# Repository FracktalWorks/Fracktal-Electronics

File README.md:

# Fracktal-Electronics
Repository for the Miscellaneous Hardware components and boards used for the additional features and other external devices

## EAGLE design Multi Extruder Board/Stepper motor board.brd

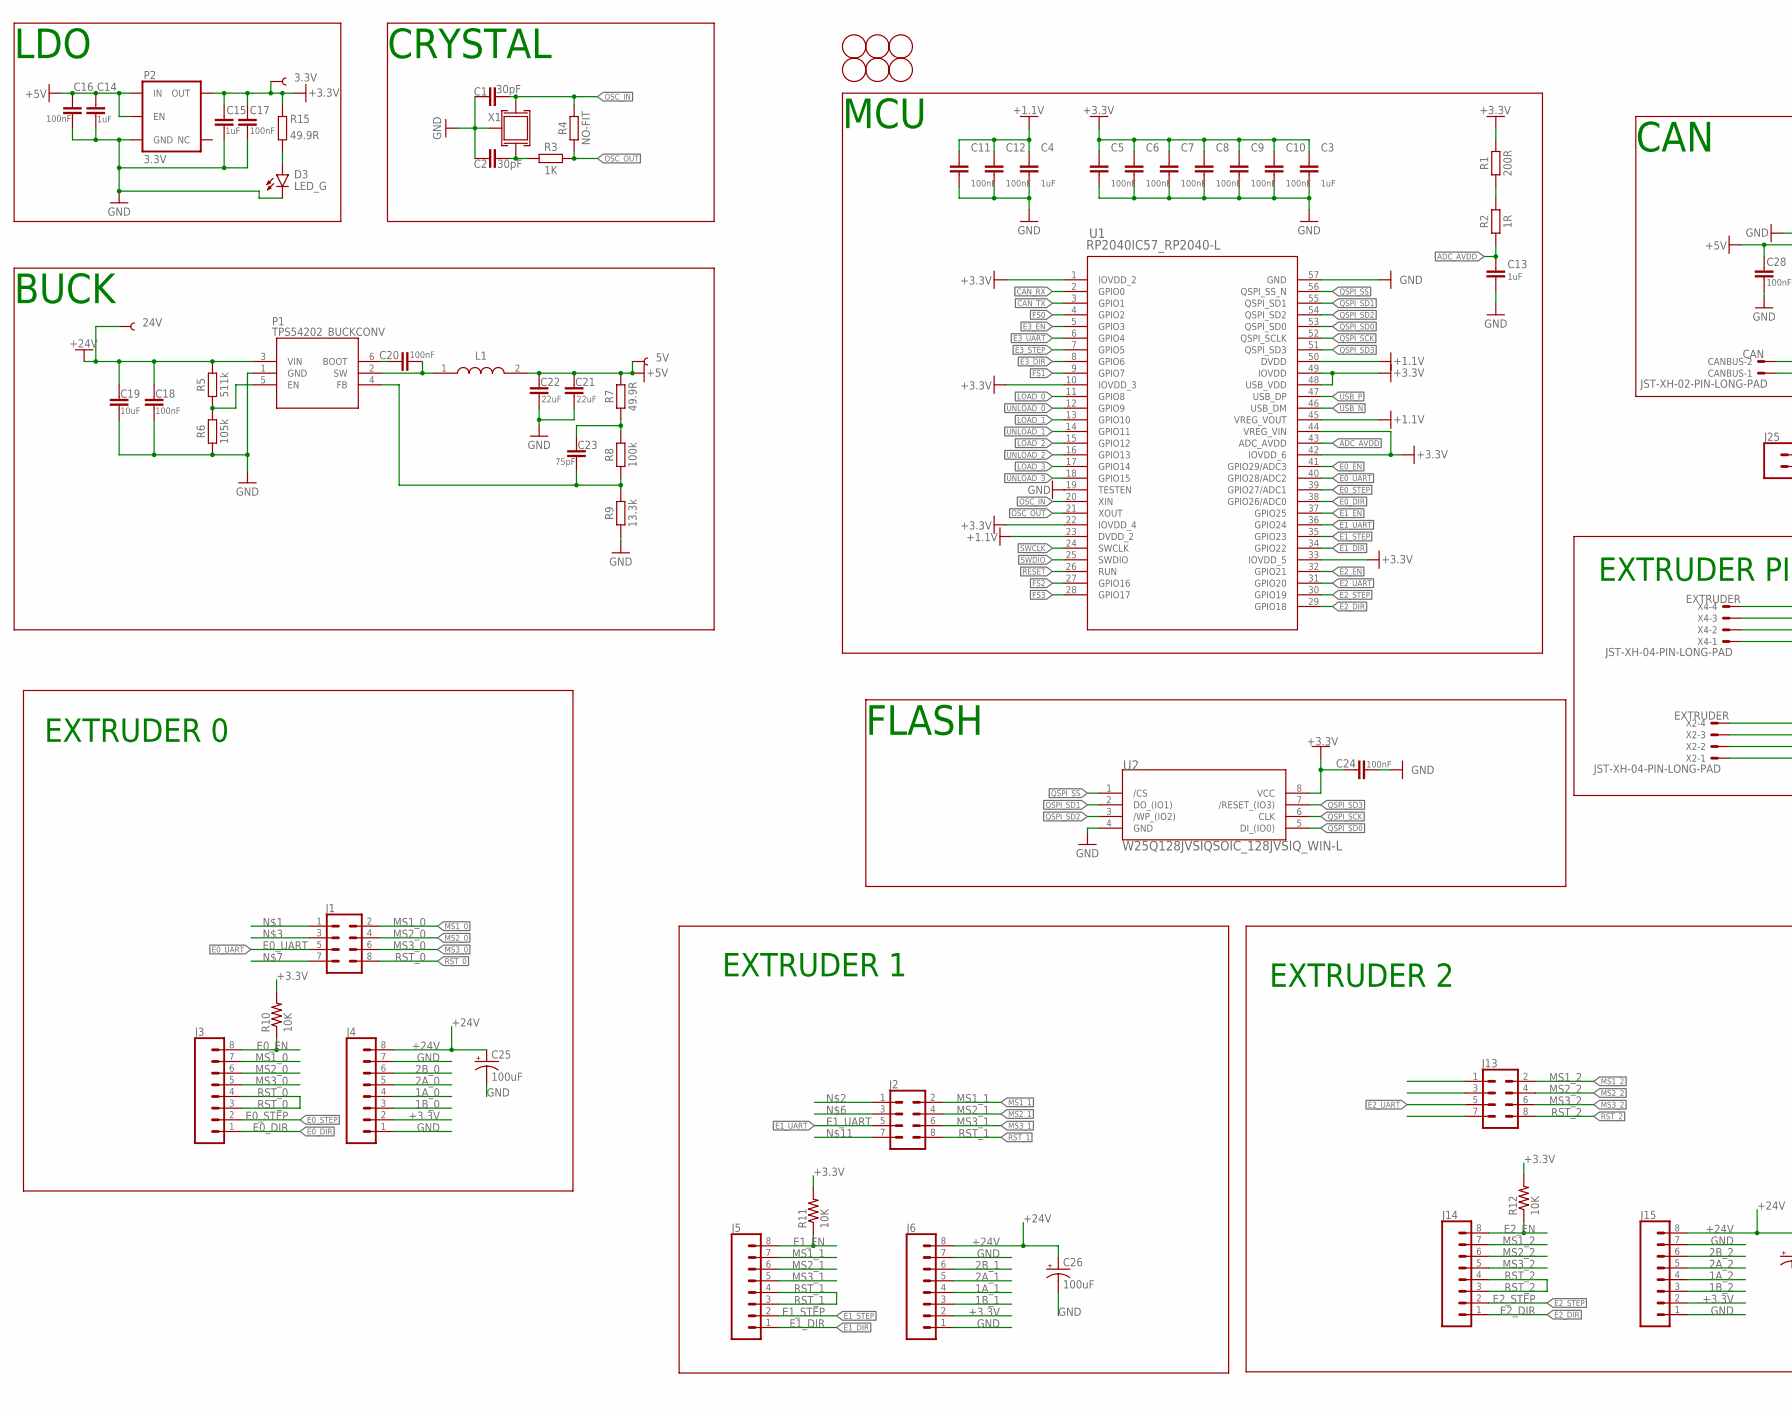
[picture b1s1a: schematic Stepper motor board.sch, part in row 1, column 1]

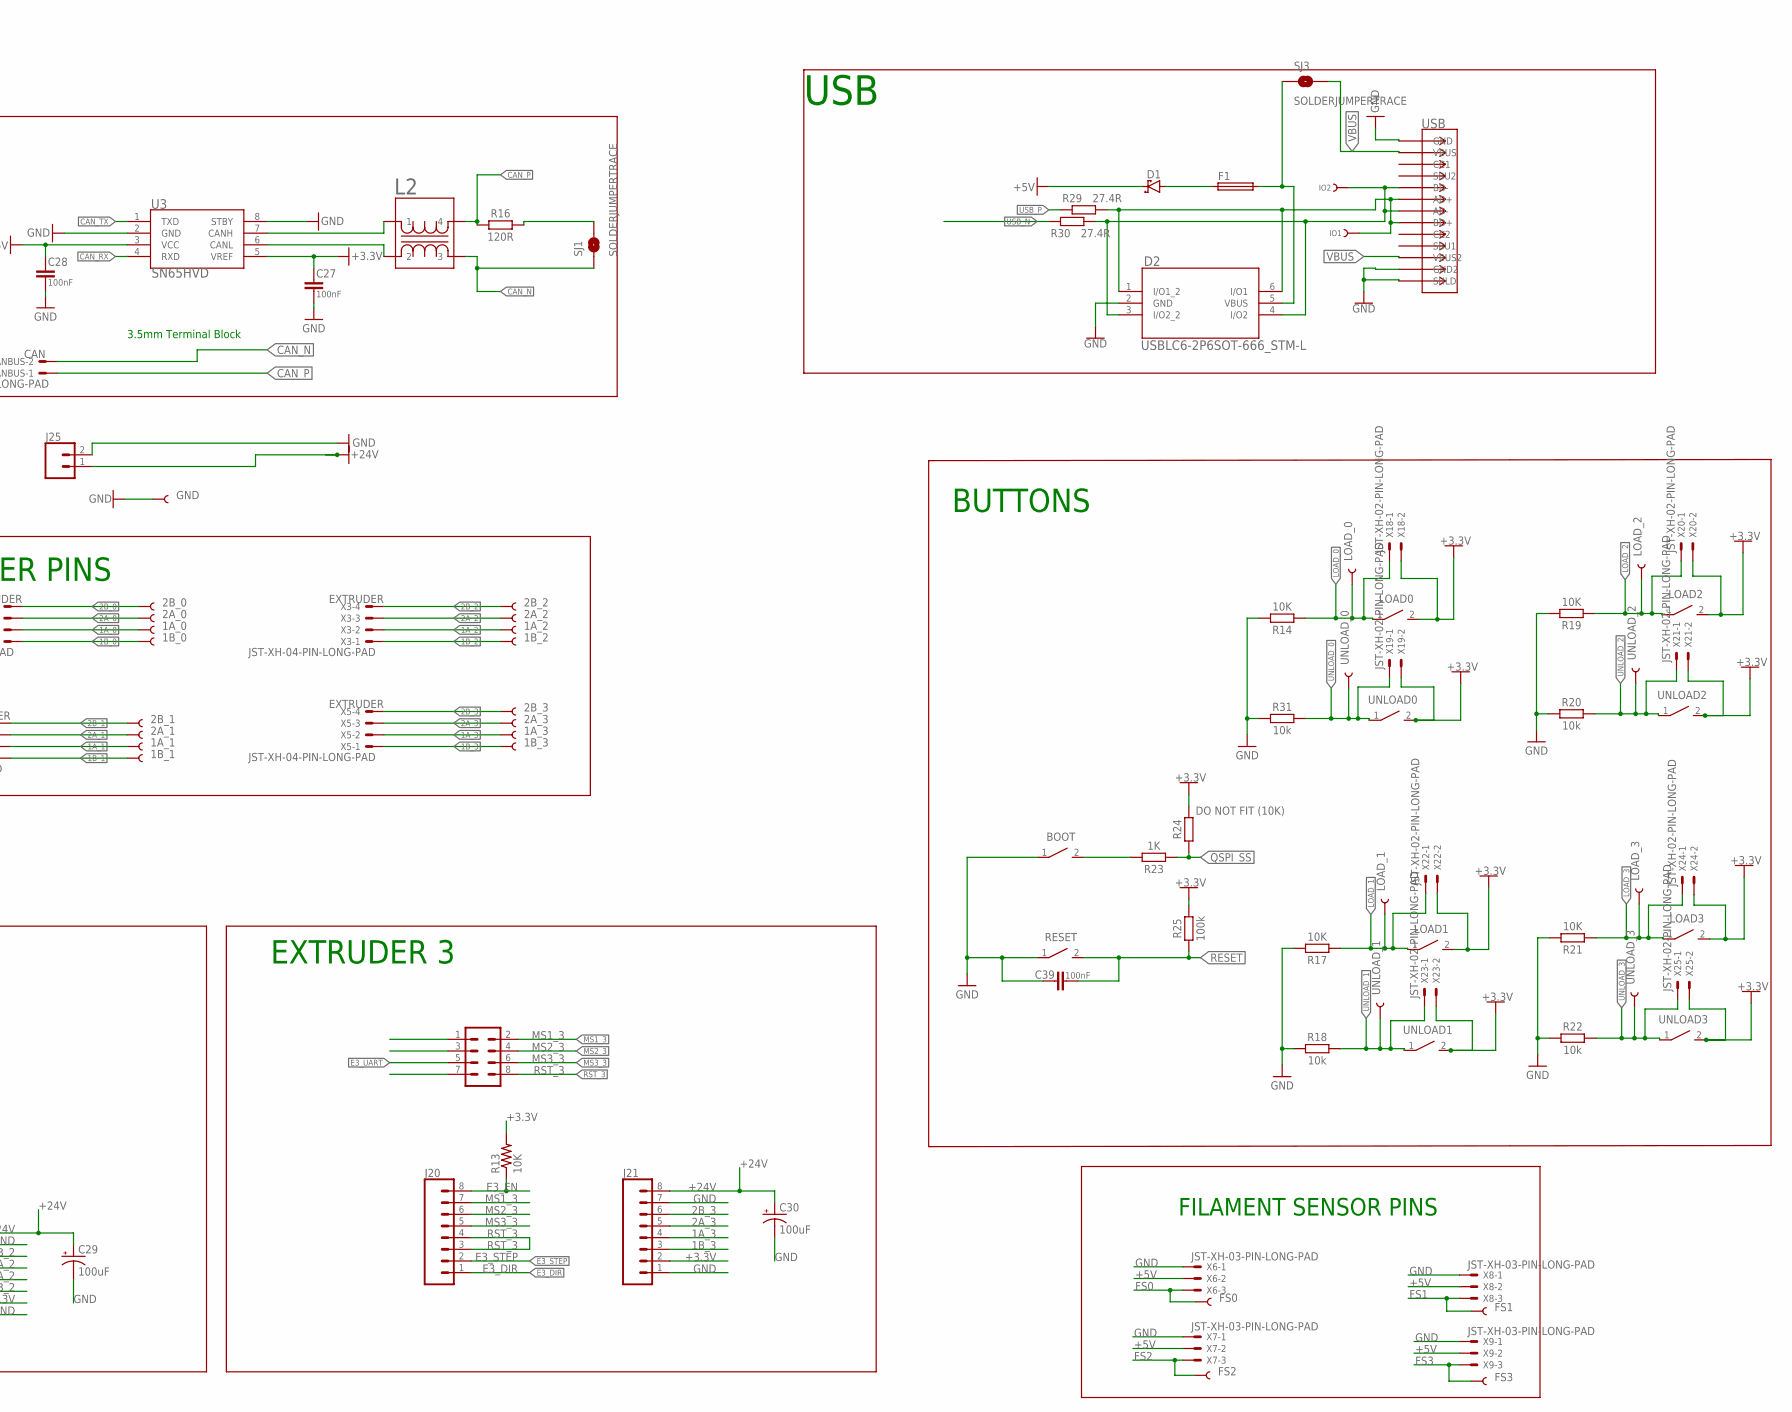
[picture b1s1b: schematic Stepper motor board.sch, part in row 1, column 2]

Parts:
1A_0, 1A_1, 1A_2, 1A_3, 1B_0, 1B_1, 1B_2, 1B_3, 2A_0, 2A_1, 2A_2, 2A_3, 2B_0, 2B_1, 2B_2, 2B_3, 3.3V, 5V, 24V: TEST-POINT3X4; PAD.03X.04
BOOT: B3U-1000P(M)-B; LCSCPN# C231329
C1, C2: 30pF; CAPC1005X60; LCSCPN# C1570
C3, C4, C13, C14, C15: 1uF; CAPC1005X60; LCSCPN# C52923
C5, C6, C7, C8, C9, C10, C11, C12, C16, C17, C18, C20, C24, C27, C28, C39: 100nF; CAPC1005X60; LCSCPN# C307331
C19: 10uF; CAPC1608X85; LCSCPN# C194427
C21, C22: 22uF; CAPC2012X110; LCSCPN# C338080
C23: 75pF; CAPC1005X60; LCSCPN# C37809
C25, C26, C29, C30: 100uF; PANASONIC_D
CANBUS: JST-XH-02-PIN-LONG-PAD; JST-XH-02-PACKAGE-LONG-PAD
D1: MBR0520LT1G; SODFL3718X115
D2: USBLC6-2P6SOT-666_STM-L; SOT-666_STM-L; LCSCPN# C2827693
D3: LED_G; LEDC1608X35N_FLAT-G; LCSCPN# C72043
F1: FUSE_CHIP-0603(1608-METRIC); FUSC1608X60N; LCSCPN# C261937
FD1, FD2, FD3, FD4, FD5, FD6: FIDUCIAL; FIDUCIAL_1MM
FS0, FS1, FS2, FS3: TEST-POINT3X4; PAD.03X.04
GND: TEST-POINT3X4; PAD.03X.04
IO1, IO2: TEST-POINT3; PAD.03X.03
J1, J2, J13, J19: CONN_04X2; 2X4
J3, J4, J5, J6, J14, J15, J20, J21: CONN_08"; 1X08
J25: CONN_023.5MM; SCREWTERMINAL-3.5MM-2
L1: ASPI-0630HI-100M-T157X7X4; SMDRI74-680MT; LCSCPN# C3000391
L2: ACM2012; ACM2012_TDK; LCSCPN# C3029258
LOAD0, LOAD1, LOAD2, LOAD3: B3U-1000P(M)-B; LCSCPN# C231329
LOAD_0, LOAD_1, LOAD_2, LOAD_3: TEST-POINT3X4; PAD.03X.04
P1: TPS54202_BUCKCONV; SOT-23-6; LCSCPN# C191884
P2: 3.3V; SOT23-5; LCSCPN# C51118
R1: 200R; RESC1005X40; LCSCPN# C25087
R2: 1R; RESC1005X40; LCSCPN# C25086
R3, R23: 1K; RESC1005X40; LCSCPN# C25543
R4: NO-FIT; RESC1005X40; LCSCPN# NO-FIT
R5: 511k; RESC1005X40; LCSCPN# C3037035
R6: 105k; RESC1005X40; LCSCPN# C2933067
R7, R15: 49.9R; RESC1005X40; LCSCPN# C25120
R8, R25: 100k; RESC1005X40; LCSCPN# C25741
R9: 13.3k; RESC1005X40; LCSCPN# C2974007
R10, R11, R12, R13: 10K; 0603-RES
R14, R17, R19, R21: 10K; RESC1005X40; LCSCPN# C25543
R16: 120R; RESC1005X40; LCSCPN# C25079
R18, R20, R22, R31: 10k; RESC1005X40
R24: DO NOT FIT (10K); RESC1005X40; LCSCPN# NO-FIT
R29, R30: 27.4R; RESC1005X40; LCSCPN# C31439
RESET: B3U-1000P(M)-B; LCSCPN# C231329
SJ1, SJ3: SOLDERJUMPERTRACE; SJ_2S-TRACE
U1: RP2040IC57_RP2040-L; IC57_RP2040-L; LCSCPN# C2040
U2: W25Q128JVSIQSOIC_128JVSIQ_WIN-L; SOIC_128JVSIQ_WIN-L; LCSCPN# C97521
U3: SN65HVD; D8-L; LCSCPN# C14019
UNLOAD0, UNLOAD1, UNLOAD2, UNLOAD3: B3U-1000P(M)-B; LCSCPN# C231329
UNLOAD_0, UNLOAD_1, UNLOAD_2, UNLOAD_3: TEST-POINT3X4; PAD.03X.04
USB: USB-C(KH-TYPE-C-16P); CONN12_KH-TYPE-C-16P; LCSCPN# C709357
X1: CRYSTAL_TAXM12M4RLBDDT2T_3225; CRYSTAL_3225; LCSCPN# C133334
X2, X3, X4, X5: JST-XH-04-PIN-LONG-PAD; JST-XH-04-PACKAGE-LONG-PAD
X6, X7, X8, X9: JST-XH-03-PIN-LONG-PAD; JST-XH-03-PACKAGE-LONG-PAD
X18, X19, X20, X21, X22, X23, X24, X25: JST-XH-02-PIN-LONG-PAD; JST-XH-02-PACKAGE-LONG-PAD

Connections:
1A_0: 1A_0.P$1, J4.4, X4.2
1A_1: 1A_1.P$1, J6.4, X2.2
1A_2: 1A_2.P$1, J15.4, X3.2
1A_3: 1A_3.P$1, J21.4, X5.2
1B_0: 1B_0.P$1, J4.3, X4.1
1B_1: 1B_1.P$1, J6.3, X2.1
1B_2: 1B_2.P$1, J15.3, X3.1
1B_3: 1B_3.P$1, J21.3, X5.1
2A_0: 2A_0.P$1, J4.5, X4.3
2A_1: 2A_1.P$1, J6.5, X2.3
2A_2: 2A_2.P$1, J15.5, X3.3
2A_3: 2A_3.P$1, J21.5, X5.3
2B_0: 2B_0.P$1, J4.6, X4.4
2B_1: 2B_1.P$1, J6.6, X2.4
2B_2: 2B_2.P$1, J15.6, X3.4
2B_3: 2B_3.P$1, J21.6, X5.4
+1.1V: C4.1, C11.1, C12.1, U1.23 (DVDD_2), U1.45 (VREG_VOUT), U1.50 (DVDD)
+3.3V: 3.3V.P$1, C3.1, C5.1, C6.1, C7.1, C8.1, C9.1, C10.1, C15.1, C17.1, C24.1, C27.1, J4.2, J6.2, J15.2, J21.2, LOAD0.2, LOAD1.2, LOAD2.2, LOAD3.2, P2.5 (OUT), R1.2, R10.2, R11.2, R12.2, R13.2, R15.2, R24.2, R25.2, U1.1 (IOVDD_2), U1.10 (IOVDD_3), U1.22 (IOVDD_4), U1.33 (IOVDD_5), U1.42 (IOVDD_6), U1.44 (VREG_VIN), U1.48 (USB_VDD), U1.49 (IOVDD), U2.8 (VCC), U3.5 (VREF), UNLOAD0.2, UNLOAD1.2, UNLOAD2.2, UNLOAD3.2, X18.2, X19.2, X20.2, X21.2, X22.2, X23.2, X24.2, X25.2
+5V: 5V.P$1, C14.1, C16.1, C21.1, C22.1, C28.1, D1.1 (C), L1.2, P2.1 (IN), P2.3 (EN), R7.2, U3.3 (VCC), X6.2, X7.2, X8.2, X9.2
+24V: 24V.P$1, C18.1, C19.1, C25.+, C26.+, C29.+, C30.+, J4.8, J6.8, J15.8, J21.8, J25.1, P1.3 (VIN), R5.2
ADC_AVDD: C13.1, R2.1, U1.43 (ADC_AVDD)
ADC_R: R1.1, R2.2
BCBOOT: C20.1, P1.6 (BOOT)
CAN1_N: L2.2, U3.6 (CANL)
CAN1_P: L2.1, U3.7 (CANH)
CAN_N: CANBUS.2, L2.3, SJ1.1
CAN_P: CANBUS.1, L2.4, R16.1
CAN_RX: U1.2 (GPIO0), U3.4 (RXD)
CAN_TX: U1.3 (GPIO1), U3.1 (TXD)
CNT: R16.2, SJ1.2
E0_DIR: J3.1, U1.38 (GPIO26/ADC0)
E0_EN: J3.8, R10.1, U1.41 (GPIO29/ADC3)
E0_STEP: J3.2, U1.39 (GPIO27/ADC1)
E0_UART: J1.5, U1.40 (GPIO28/ADC2)
E1_DIR: J5.1, U1.34 (GPIO22)
E1_EN: J5.8, R11.1, U1.37 (GPIO25)
E1_STEP: J5.2, U1.35 (GPIO23)
E1_UART: J2.5, U1.36 (GPIO24)
E2_DIR: J14.1, U1.29 (GPIO18)
E2_EN: J14.8, R12.1, U1.32 (GPIO21)
E2_STEP: J14.2, U1.30 (GPIO19)
E2_UART: J13.5, U1.31 (GPIO20)
E3_DIR: J20.1, U1.8 (GPIO6)
E3_EN: J20.8, R13.1, U1.5 (GPIO3)
E3_STEP: J20.2, U1.7 (GPIO5)
E3_UART: J19.5, U1.6 (GPIO4)
FS0: FS0.P$1, U1.4 (GPIO2), X6.3
FS1: FS1.P$1, U1.9 (GPIO7), X8.3
FS2: FS2.P$1, U1.27 (GPIO16), X7.3
FS3: FS3.P$1, U1.28 (GPIO17), X9.3
GND: BOOT.1, C1.2, C2.1, C3.2, C4.2, C5.2, C6.2, C7.2, C8.2, C9.2, C10.2, C11.2, C12.2, C13.2, C14.2, C15.2, C16.2, C17.2, C18.2, C19.2, C21.2, C22.2, C24.2, C25.-, C26.-, C27.2, C28.2, C29.-, C30.-, C39.1, D2.2 (GND), D3.C, GND.P$1, J4.1, J4.7, J6.1, J6.7, J15.1, J15.7, J21.1, J21.7, J25.2, P1.1 (GND), P2.2 (GND), R6.1, R9.1, R14.2, R17.2, R18.1, R19.2, R20.1, R21.2, R22.1, R31.1, RESET.1, U1.19 (TESTEN), U1.57 (GND), U2.4 (GND), U3.2 (GND), U3.8 (STBY), USB.1 (GND), USB.12 (GND2), USB.13 (SHLD), USB.14 (SHLD), USB.15 (SHLD), USB.16 (SHLD), USB.18 (SHLD), USB.19 (SHLD), USB.20 (SHLD), USB.21 (SHLD), USB.24 (SHLD), USB.25 (SHLD), USB.26 (SHLD), USB.27 (SHLD), USB.28 (SHLD), USB.29 (SHLD), USB.37 (SHLD), USB.39 (SHLD), USB.41 (SHLD), USB.43 (SHLD), X1.P$2 (GND), X1.P$4 (GND), X6.1, X7.1, X8.1, X9.1
LDOLED: D3.A, R15.1
LOAD_0: LOAD0.1, LOAD_0.P$1, R14.1, U1.11 (GPIO8), X18.1
LOAD_1: LOAD1.1, LOAD_1.P$1, R17.1, U1.13 (GPIO10), X22.1
LOAD_2: LOAD2.1, LOAD_2.P$1, R19.1, U1.15 (GPIO12), X20.1
LOAD_3: LOAD3.1, LOAD_3.P$1, R21.1, U1.17 (GPIO14), X24.1
MS1_0: J1.2, J3.7
MS1_1: J2.2, J5.7
MS1_2: J13.2, J14.7
MS1_3: J19.2, J20.7
MS2_0: J1.4, J3.6
MS2_1: J2.4, J5.6
MS2_2: J13.4, J14.6
MS2_3: J19.4, J20.6
MS3_0: J1.6, J3.5
MS3_1: J2.6, J5.5
MS3_2: J13.6, J14.5
MS3_3: J19.6, J20.5
OSC_IN: C1.1, R4.2, U1.20 (XIN), X1.P$1 (P1)
OSC_OUT: R3.2, R4.1, U1.21 (XOUT)
QSPI_SCK: U1.52 (QSPI_SCLK), U2.6 (CLK)
QSPI_SD0: U1.53 (QSPI_SD0), U2.5 (DI_(IO0))
QSPI_SD1: U1.55 (QSPI_SD1), U2.2 (DO_(IO1))
QSPI_SD2: U1.54 (QSPI_SD2), U2.3 (/WP_(IO2))
QSPI_SD3: U1.51 (QSPI_SD3), U2.7 (/RESET_(IO3))
QSPI_SS: R23.1, R24.1, U1.56 (QSPI_SS_N), U2.1 (/CS)
RESET: C39.2, R25.1, RESET.2, U1.26 (RUN)
RST_0: J1.8, J3.3, J3.4
RST_1: J2.8, J5.3, J5.4
RST_2: J13.8, J14.3, J14.4
RST_3: J19.8, J20.3, J20.4
SWB: BOOT.2, R23.2
SWCLK: U1.24 (SWCLK)
SWDIO: U1.25 (SWDIO)
UNLOAD_0: R31.2, U1.12 (GPIO9), UNLOAD0.1, UNLOAD_0.P$1, X19.1
UNLOAD_1: R18.2, U1.14 (GPIO11), UNLOAD1.1, UNLOAD_1.P$1, X23.1
UNLOAD_2: R20.2, U1.16 (GPIO13), UNLOAD2.1, UNLOAD_2.P$1, X21.1
UNLOAD_3: R22.2, U1.18 (GPIO15), UNLOAD3.1, UNLOAD_3.P$1, X25.1
USB1_N: D2.3 (I/O2_2), D2.4 (I/O2), IO2.P$1, R30.1, USB.5 (BD-), USB.7 (AD-)
USB1_P: D2.1 (I/O1_2), D2.6 (I/O1), IO1.P$1, R29.1, USB.6 (AD+), USB.8 (BD+)
USB_N: R30.2, U1.46 (USB_DM)
USB_P: R29.2, U1.47 (USB_DP)
VBUS: SJ3.2, USB.2 (VBUS), USB.11 (VBUS2)
VBUS1: D2.5 (VBUS), F1.2, SJ3.1
VBUS3: D1.2 (A), F1.1
VRC: C23.1, R7.1, R8.2
VREGEN: P1.5 (EN), R5.1, R6.2
VREGFB: C23.2, P1.4 (FB), R8.1, R9.2
VREGO: C20.2, L1.1, P1.2 (SW)
XR: C2.2, R3.1, X1.P$3 (P2)

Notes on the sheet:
MCU
FLASH
LDO
BUCK
CRYSTAL
CAN
3.5mm Terminal Block
USB
EXTRUDER 0
EXTRUDER 1
EXTRUDER 2
EXTRUDER 3
BUTTONS
EXTRUDER PINS
FILAMENT SENSOR PINS

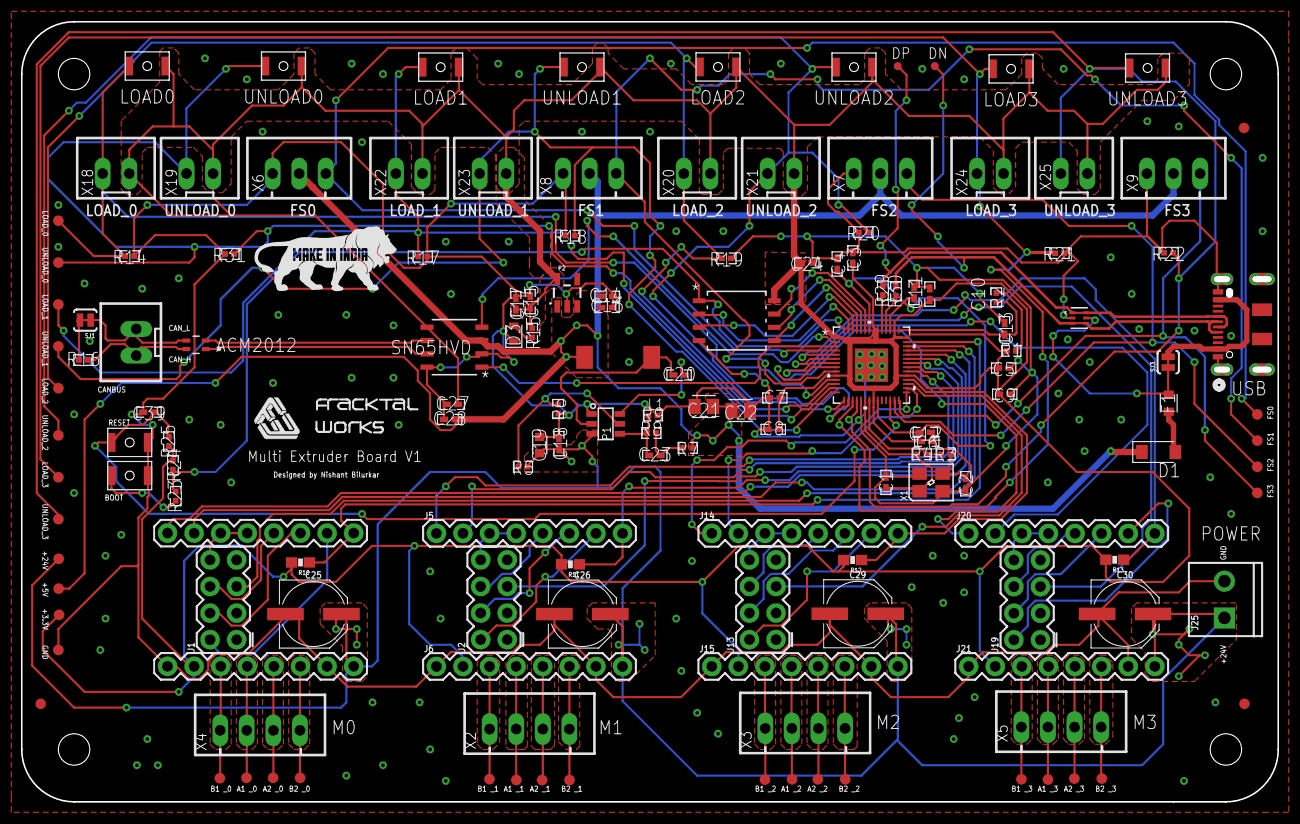
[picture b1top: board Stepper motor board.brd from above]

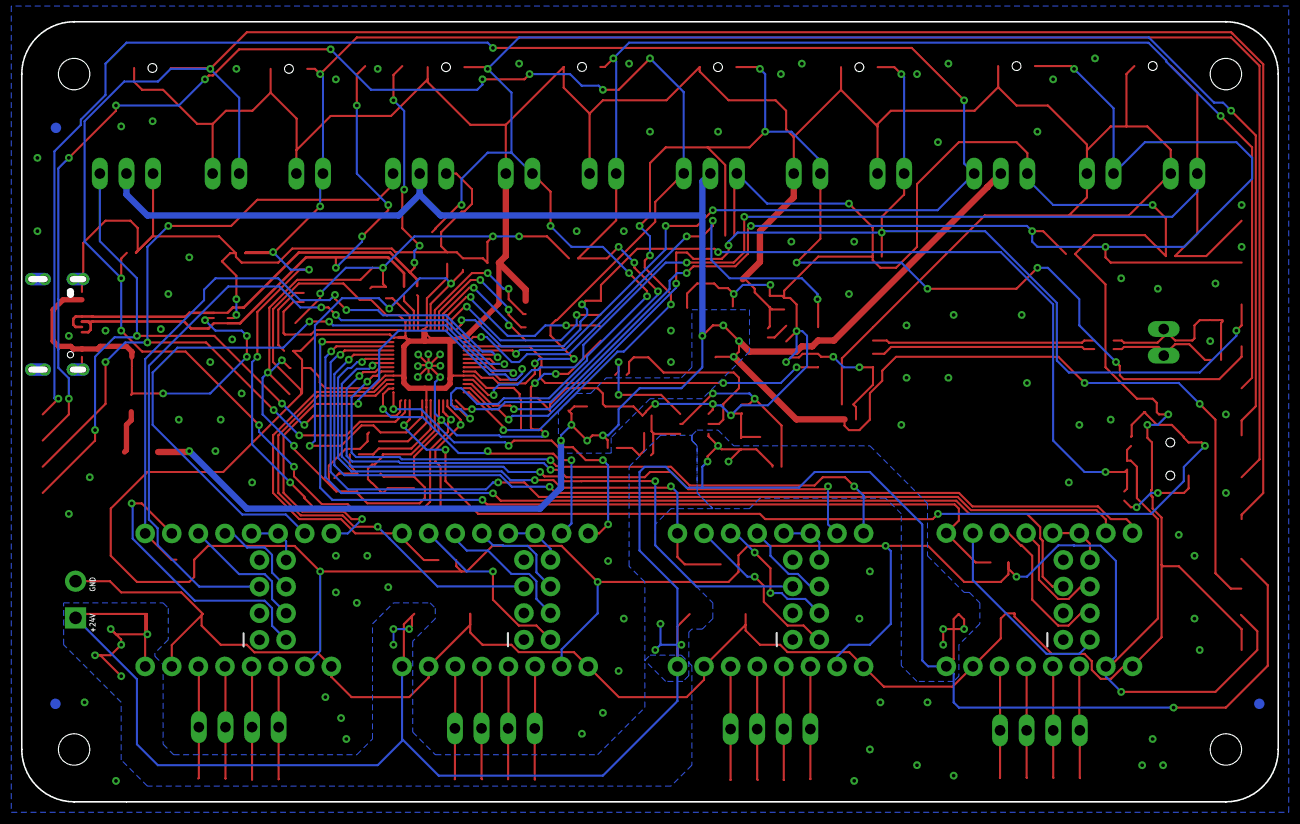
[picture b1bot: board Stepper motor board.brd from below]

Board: 2 copper layers, 120.0 x 74.5 mm, 156 parts (3 on the bottom side), 98 nets.

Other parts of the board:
U$2: MAKEININDIA
U$3: FWLOGO_SMALL

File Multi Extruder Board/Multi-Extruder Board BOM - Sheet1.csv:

Qty,Designator,Footprint,Device,LCSC Part #,Description,Value
1,J25,SCREWTERMINAL-3.5MM-2,CONN_023.5MM,,Multi connection point. Often used as Generic Header-pin footprint for 0.1 inch spaced/style header connections,
4,"J1, J2, J13, J19",2X4,CONN_04X2,,Multi connection point. Often used as Generic Header-pin footprint for 0.1 inch spaced/style header connections,
8,Multi connection point. Often used as Generic Header-pin footprint for 0.1 inch spaced/style header connections,"J3, J4, J5, J6, J14, J15, J20, J21","CONN_08"";1X08""",,,
2,"R8, R25",RESC1005X40,R_CHIP-0402(1005-METRIC),C25741,Resistor Fixed - Generic,100k
16,"C5, C6, C7, C8, C9, C10, C11, C12, C16, C17, C18, C20, C24, C27, C28, C39",CAPC1005X60,C_CHIP-0402(1005-METRIC),C307331,Capacitor - Generic,100nF
4,"C25, C26, C29, C30",PANASONIC_D,100UF-POLAR-25V-20%(ELEC),,100µF polarized capacitors,100uF
1,R6,RESC1005X40,R_CHIP-0402(1005-METRIC),C2933067,Resistor Fixed - Generic,105k
4,"R10, R11, R12, R13",0603-RES,10KOHM1/10W1%(0603)0603,,RES-00824,10K
4,"R14, R17, R19, R21",RESC1005X40,R_CHIP-0402(1005-METRIC),C25543,Resistor Fixed - Generic,10K
4,"R18, R20, R22, R31",RESC1005X40,R_CHIP-0402(1005-METRIC),,Resistor Fixed - Generic,10k
1,C19,CAPC1608X85,C_CHIP-0603(1608-METRIC),C194427,Capacitor - Generic,10uF
1,R16,RESC1005X40,R_CHIP-0402(1005-METRIC),C25079,Resistor Fixed - Generic,120R
1,R9,RESC1005X40,R_CHIP-0402(1005-METRIC),C2974007,Resistor Fixed - Generic,13.3k
2,"R3, R23",RESC1005X40,R_CHIP-0402(1005-METRIC),C25543,Resistor Fixed - Generic,1K
1,R2,RESC1005X40,R_CHIP-0402(1005-METRIC),C25086,Resistor Fixed - Generic,1R
5,"C3, C4, C13, C14, C15",CAPC1005X60,C_CHIP-0402(1005-METRIC),C52923,Capacitor - Generic,1uF
1,R1,RESC1005X40,R_CHIP-0402(1005-METRIC),C25087,Resistor Fixed - Generic,200R
2,"C21, C22",CAPC2012X110,C_CHIP-0805(2012-METRIC),C338080,Capacitor - Generic,22uF
2,"R29, R30",RESC1005X40,R_CHIP-0402(1005-METRIC),C31439,Resistor Fixed - Generic,27.4R
1,P2,SOT23-5,V_REG_AP2112K-3.3V,C51118,AP2112 - 600mA CMOS LDO Regulator w/ Enable,3.3V
2,"C1, C2",CAPC1005X60,C_CHIP-0402(1005-METRIC),C1570,Capacitor - Generic,30pF
2,"R7, R15",RESC1005X40,R_CHIP-0402(1005-METRIC),C25120,Resistor Fixed - Generic,49.9R
1,R5,RESC1005X40,R_CHIP-0402(1005-METRIC),C3037035,Resistor Fixed - Generic,511k
1,C23,CAPC1005X60,C_CHIP-0402(1005-METRIC),C37809,Capacitor - Generic,75pF
1,L2,ACM2012_TDK,ACM2012-201-2P-T002ACM2012_TDK,C3029258,,ACM2012
1,L1,SMDRI74-680MT,ASPI-0630HI-100M-T157X7X4,C3000391,Inductor Power Molded Wirewound 10uH 20% 3A 105mOhm DCR T/R,ASPI-0630HI-100M-T157X7X4
10,"BOOT, LOAD0, LOAD1, LOAD2, LOAD3, RESET, UNLOAD0, UNLOAD1, UNLOAD2, UNLOAD3",B3U-1000P(M)-B,B3U-X000B3U-1000P(M)-B1000P(M)-B,C231329,Ultra-small Tactile Switch,B3U-1000P(M)-B
1,X1,CRYSTAL_3225,CRYSTAL_TAXM12M4RLBDDT2T_3225,C133334,,CRYSTAL_TAXM12M4RLBDDT2T_3225
1,R24,RESC1005X40,R_CHIP-0402(1005-METRIC),NO-FIT,Resistor Fixed - Generic,DO NOT FIT (10K)
6,"FD1, FD2, FD3, FD4, FD5, FD6",FIDUCIAL_1MM,FIDUCIAL,,"For use by pick and place machines to calibrate the vision/machine, 1mm",FIDUCIAL
1,F1,FUSC1608X60N,FUSE_CHIP-0603(1608-METRIC),C261937,Fuse - Generic,FUSE_CHIP-0603(1608-METRIC)
9,"CANBUS, X18, X19, X20, X21, X22, X23, X24, X25",JST-XH-02-PACKAGE-LONG-PAD,JST-XH-02-PIN-LONG-PAD,,JST XH Connector 2 Pin,JST-XH-02-PIN-LONG-PAD
4,"X6, X7, X8, X9",JST-XH-03-PACKAGE-LONG-PAD,JST-XH-03-PIN-LONG-PAD,,JST XH Connector 2 Pin,JST-XH-03-PIN-LONG-PAD
4,"X2, X3, X4, X5",JST-XH-04-PACKAGE-LONG-PAD,JST-XH-04-PIN-LONG-PAD,,JST XH Connector 2 Pin,JST-XH-04-PIN-LONG-PAD
1,D3,LEDC1608X35N_FLAT-G,CHIP-FLAT-G_0603-0.35MM,C72043,,LED_G
1,D1,SODFL3718X115,SCHOTTKY_MBR0520LT1GDO-219,,Schottky Diode - Popular parts,MBR0520LT1G
1,R4,RESC1005X40,R_CHIP-0402(1005-METRIC),NO-FIT,Resistor Fixed - Generic,NO-FIT
1,U1,IC57_RP2040-L,RP2040IC57_RP2040-L,C2040,,RP2040IC57_RP2040-L
1,U3,D8-L,SN65HVD1050DRD8-L,C14019,,SN65HVD
2,"SJ1, SJ3",SJ_2S-TRACE,SOLDERJUMPERTRACE,,Solder Jumper,SOLDERJUMPERTRACE
2,"IO1, IO2",PAD.03X.03,TEST-POINT3,,SparkFun Test Points,TEST-POINT3
32,"1A_0, 1A_1, 1A_2, 1A_3, 1B_0, 1B_1, 1B_2, 1B_3, 2A_0, 2A_1, 2A_2, 2A_3, 2B_0, 2B_1, 2B_2, 2B_3, 3.3V, 5V, 24V, FS0, FS1, FS2, FS3, GND, LOAD_0, LOAD_1, LOAD_2, LOAD_3, UNLOAD_0, UNLOAD_1, UNLOAD_2, UNLOAD_3",PAD.03X.04,TEST-POINT3X4,,SparkFun Test Points,TEST-POINT3X4
1,P1,SOT-23-6,TPS54202_BUCKCONV,C191884,,TPS54202_BUCKCONV
1,USB,CONN12_KH-TYPE-C-16P,USB-C(KH-TYPE-C-16P),C709357,Shenzhen Kinghelm Elec KH-TYPE-C-16P,USB-C(KH-TYPE-C-16P)
1,D2,SOT-666_STM-L,USBLC6-2P6SOT-666_STM-L,C2827693,,USBLC6-2P6SOT-666_STM-L
1,U2,SOIC_128JVSIQ_WIN-L,W25Q128JVSIQSOIC_128JVSIQ_WIN-L,C97521,,W25Q128JVSIQSOIC_128JVSIQ_WIN-L

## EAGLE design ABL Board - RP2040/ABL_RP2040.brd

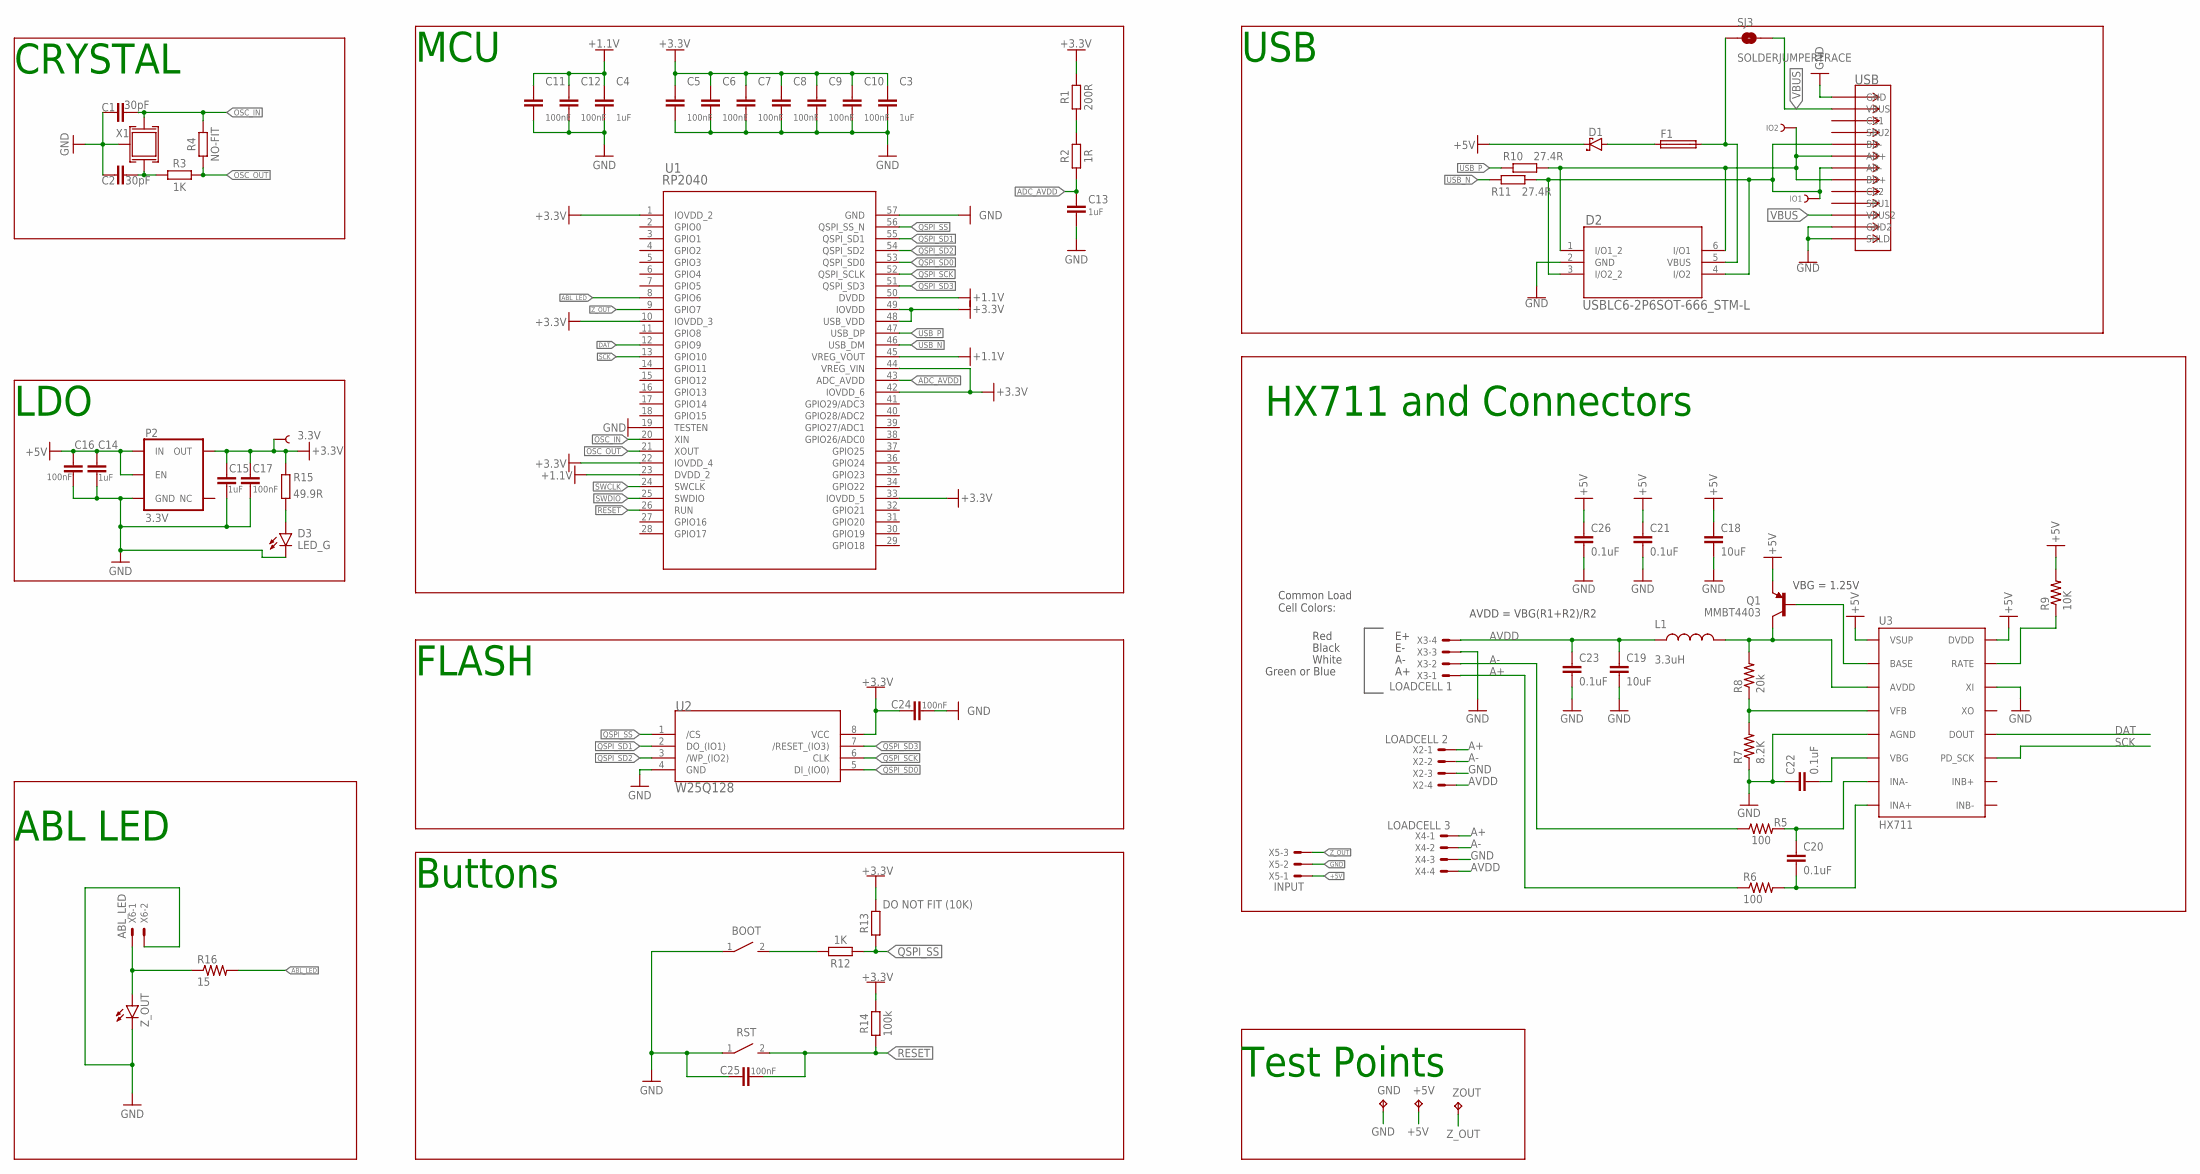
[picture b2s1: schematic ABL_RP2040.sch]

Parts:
3.3V: TEST-POINT3X4; PAD.03X.04
+5V: TPB2,54; B2,54
BOOT: B3U-1000P(M)-B; LCSCPN# C231329
C1, C2: 30pF; CAPC1005X60; LCSCPN# C1570
C3, C4, C13, C14, C15: 1uF; CAPC1005X60; LCSCPN# C52923
C5, C6, C7, C8, C9, C10, C11, C12, C16, C17, C24, C25: 100nF; CAPC1005X60; LCSCPN# C307331
C18, C19: 10uF; 1210
C20, C21, C22, C23, C26: 0.1uF; 0603-CAP
D1: MBR0520LT1G; SODFL3718X115
D2: USBLC6-2P6SOT-666_STM-L; SOT-666_STM-L; LCSCPN# C2827693
D3: LED_G; LEDC1608X35N_FLAT-G; LCSCPN# C72043
F1: FUSE_CHIP-0603(1608-METRIC); FUSC1608X60N; LCSCPN# C261937
GND: TPB2,54; B2,54
IO1, IO2: TEST-POINT3; PAD.03X.03
L1: 3.3uH; 0805
P2: 3.3V; SOT23-5; LCSCPN# C51118
Q1: MMBT4403; SOT23-3
R1: 200R; RESC1005X40; LCSCPN# C25087
R2: 1R; RESC1005X40; LCSCPN# C25086
R3, R12: 1K; RESC1005X40; LCSCPN# C25543
R4: NO-FIT; RESC1005X40; LCSCPN# NO-FIT
R5, R6: 100; 0603-RES@1
R7: 8.2K; 0603-RES
R8: 20k; 0603-RES
R9: 10K; 0603-RES@1
R10, R11: 27.4R; RESC1005X40; LCSCPN# C31439
R13: DO NOT FIT (10K); RESC1005X40; LCSCPN# NO-FIT
R14: 100k; RESC1005X40; LCSCPN# C25741
R15: 49.9R; RESC1005X40; LCSCPN# C25120
R16: 15; 0603-RES
RST: B3U-1000P(M)-B; LCSCPN# C231329
SJ3: SOLDERJUMPERTRACE; SJ_2S-TRACE
U1: RP2040; IC57_RP2040-L; LCSCPN# C2040
U2: W25Q128; SOIC_128JVSIQ_WIN-L; LCSCPN# C97521
U3: HX711; SO16
USB: USB-C(KH-TYPE-C-16P); CONN12_KH-TYPE-C-16P; LCSCPN# C709357
X1: CRYSTAL_TAXM12M4RLBDDT2T_3225; CRYSTAL_3225; LCSCPN# C133334
X2: LOADCELL 2; JST-XH-04-PACKAGE-LONG-PAD
X3: LOADCELL 1; JST-XH-04-PACKAGE-LONG-PAD
X4: LOADCELL 3; JST-XH-04-PACKAGE-LONG-PAD
X5: INPUT; JST-XH-03-PACKAGE-LONG-PAD
X6: ABL_LED; JST-XH-02-PACKAGE-LONG-PAD
ZOUT: TPB2,54; B2,54
Z_OUT: LEDSML0603; SML0603

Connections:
+1.1V: C4.1, C11.1, C12.1, U1.23 (DVDD_2), U1.45 (VREG_VOUT), U1.50 (DVDD)
+3.3V: 3.3V.P$1, C3.1, C5.1, C6.1, C7.1, C8.1, C9.1, C10.1, C15.1, C17.1, C24.1, P2.5 (OUT), R1.2, R13.2, R14.2, R15.2, U1.1 (IOVDD_2), U1.10 (IOVDD_3), U1.22 (IOVDD_4), U1.33 (IOVDD_5), U1.42 (IOVDD_6), U1.44 (VREG_VIN), U1.48 (USB_VDD), U1.49 (IOVDD), U2.8 (VCC)
+5V: +5V.TP, C14.1, C16.1, C18.1, C21.1, C26.1, D1.1 (C), P2.1 (IN), P2.3 (EN), Q1.2 (E), R9.2, U3.1 (VSUP), U3.16 (DVDD), X5.1
A+: R6.1, X2.1, X3.1, X4.1
A-: R5.1, X2.2, X3.2, X4.2
ABL_LED: R16.2, U1.8 (GPIO6)
ADC_AVDD: C13.1, R2.1, U1.43 (ADC_AVDD)
ADC_R: R1.1, R2.2
AVDD: C19.1, C23.1, L1.1, X2.4, X3.4, X4.4
DAT: U1.12 (GPIO9), U3.12 (DOUT)
GND: BOOT.1, C1.2, C2.1, C3.2, C4.2, C5.2, C6.2, C7.2, C8.2, C9.2, C10.2, C11.2, C12.2, C13.2, C14.2, C15.2, C16.2, C17.2, C18.2, C19.2, C21.2, C22.1, C23.2, C24.2, C25.1, C26.2, D2.2 (GND), D3.C, GND.TP, P2.2 (GND), R7.1, RST.1, U1.19 (TESTEN), U1.57 (GND), U2.4 (GND), U3.5 (AGND), U3.14 (XI), USB.1 (GND), USB.12 (GND2), USB.13 (SHLD), USB.14 (SHLD), USB.15 (SHLD), USB.16 (SHLD), USB.18 (SHLD), USB.19 (SHLD), USB.20 (SHLD), USB.21 (SHLD), USB.24 (SHLD), USB.25 (SHLD), USB.26 (SHLD), USB.27 (SHLD), USB.28 (SHLD), USB.29 (SHLD), USB.37 (SHLD), USB.39 (SHLD), USB.41 (SHLD), USB.43 (SHLD), X1.P$2 (GND), X1.P$4 (GND), X2.3, X3.3, X4.3, X5.2, X6.2, Z_OUT.C
LDOLED: D3.A, R15.1
unnamed: R9.1, U3.15 (RATE)
unnamed: C20.1, R5.2, U3.7 (INA-)
unnamed: C20.2, R6.2, U3.8 (INA+)
unnamed: Q1.1 (B), U3.2 (BASE)
unnamed: L1.2, Q1.3 (C), R8.2, U3.3 (AVDD)
unnamed: R7.2, R8.1, U3.4 (VFB)
unnamed: C22.2, U3.6 (VBG)
unnamed: R16.1, X6.1, Z_OUT.A
OSC_IN: C1.1, R4.2, U1.20 (XIN), X1.P$1 (P1)
OSC_OUT: R3.2, R4.1, U1.21 (XOUT)
QSPI_SCK: U1.52 (QSPI_SCLK), U2.6 (CLK)
QSPI_SD0: U1.53 (QSPI_SD0), U2.5 (DI_(IO0))
QSPI_SD1: U1.55 (QSPI_SD1), U2.2 (DO_(IO1))
QSPI_SD2: U1.54 (QSPI_SD2), U2.3 (/WP_(IO2))
QSPI_SD3: U1.51 (QSPI_SD3), U2.7 (/RESET_(IO3))
QSPI_SS: R12.1, R13.1, U1.56 (QSPI_SS_N), U2.1 (/CS)
RESET: C25.2, R14.1, RST.2, U1.26 (RUN)
SCK: U1.13 (GPIO10), U3.11 (PD_SCK)
SWB: BOOT.2, R12.2
SWCLK: U1.24 (SWCLK)
SWDIO: U1.25 (SWDIO)
USB1_N: D2.3 (I/O2_2), D2.4 (I/O2), IO1.P$1, R11.1, USB.5 (BD-), USB.7 (AD-)
USB1_P: D2.1 (I/O1_2), D2.6 (I/O1), IO2.P$1, R10.1, USB.6 (AD+), USB.8 (BD+)
USB_N: R11.2, U1.46 (USB_DM)
USB_P: R10.2, U1.47 (USB_DP)
VBUS: SJ3.2, USB.2 (VBUS), USB.11 (VBUS2)
VBUS1: D2.5 (VBUS), F1.2, SJ3.1
VBUS3: D1.2 (A), F1.1
XR: C2.2, R3.1, X1.P$3 (P2)
Z_OUT: U1.9 (GPIO7), X5.3, ZOUT.TP

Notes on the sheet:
LDO
CRYSTAL
MCU
FLASH
Buttons
USB
VBG = 1.25V
AVDD = VBG(R1+R2)/R2
Red
Black
White
Green or Blue
Common Load Cell Colors:
HX711 and Connectors
Test Points
ABL LED

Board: 2 copper layers, 69 parts (0 on the bottom side), 40 nets, no tracks yet.

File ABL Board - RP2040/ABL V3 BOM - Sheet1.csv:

Qty,Designator,Footprint,Comment,LCSC Part #,Description,Value
1,Z_OUT,SML0603,LEDSML0603,,LED,
5,"C20, C21, C22, C23, C26",0603-CAP,0.1UF-25V-5%(0603),,CAP-08604,0.1uF
2,"R5, R6",0603-RES@1,100OHM-1/10W-1%(0603),,RES-07863,100
1,R14,RESC1005X40,R_CHIP-0402(1005-METRIC),,Resistor Fixed - Generic,100k
12,"C5, C6, C7, C8, C9, C10, C11, C12, C16, C17, C24, C25",CAPC1005X60,C_CHIP-0402(1005-METRIC),,Capacitor - Generic,100nF
1,R9,0603-RES@1,10KOHM-1/10W-1%(0603)0603,,RES-00824,10K
2,"C18, C19",1210,10UF50V20%(1210),,CAP-09824,10uF
1,R16,0603-RES,RESISTOR0603,,Resistor,15
2,"R3, R12",RESC1005X40,R_CHIP-0402(1005-METRIC),,Resistor Fixed - Generic,1K
1,R2,RESC1005X40,R_CHIP-0402(1005-METRIC),,Resistor Fixed - Generic,1R
5,"C3, C4, C13, C14, C15",CAPC1005X60,C_CHIP-0402(1005-METRIC),,Capacitor - Generic,1uF
1,R1,RESC1005X40,R_CHIP-0402(1005-METRIC),,Resistor Fixed - Generic,200R
1,R8,0603-RES,20KOHM1/10W1%(0603),,RES-09383,20k
2,"R10, R11",RESC1005X40,R_CHIP-0402(1005-METRIC),,Resistor Fixed - Generic,27.4R
1,P2,SOT23-5,V_REG_AP2112K-3.3V,,AP2112 - 600mA CMOS LDO Regulator w/ Enable,3.3V
1,L1,805,INDUCTOR0805-IND,,Inductors,3.3uH
2,"C1, C2",CAPC1005X60,C_CHIP-0402(1005-METRIC),,Capacitor - Generic,30pF
1,R15,RESC1005X40,R_CHIP-0402(1005-METRIC),,Resistor Fixed - Generic,49.9R
1,R7,0603-RES,8.2KOHM-1/10W-5%(0603),,RES-10646,8.2K
1,X6,JST-XH-02-PACKAGE-LONG-PAD,JST-XH-02-PIN-LONG-PAD,,JST XH Connector 2 Pin,ABL_LED
2,"BOOT, RST",B3U-1000P(M)-B,B3U-X000B3U-1000P(M)-B1000P(M)-B,,Ultra-small Tactile Switch,B3U-1000P(M)-B
1,X1,CRYSTAL_3225,CRYSTAL_TAXM12M4RLBDDT2T_3225,,,CRYSTAL_TAXM12M4RLBDDT2T_3225
1,R13,RESC1005X40,R_CHIP-0402(1005-METRIC),,Resistor Fixed - Generic,DO NOT FIT (10K)
1,F1,FUSC1608X60N,FUSE_CHIP-0603(1608-METRIC),,Fuse - Generic,FUSE_CHIP-0603(1608-METRIC)
1,U3,SO16,HX711HX711,,,HX711
1,X5,JST-XH-03-PACKAGE-LONG-PAD,JST-XH-03-PIN-LONG-PAD,,JST XH Connector 2 Pin,INPUT
1,D3,LEDC1608X35N_FLAT-G,CHIP-FLAT-G_0603-0.35MM,,,LED_G
1,X3,JST-XH-04-PACKAGE-LONG-PAD,JST-XH-04-PIN-LONG-PAD,,JST XH Connector 2 Pin,LOADCELL 1
1,X2,JST-XH-04-PACKAGE-LONG-PAD,JST-XH-04-PIN-LONG-PAD,,JST XH Connector 2 Pin,LOADCELL 2
1,X4,JST-XH-04-PACKAGE-LONG-PAD,JST-XH-04-PIN-LONG-PAD,,JST XH Connector 2 Pin,LOADCELL 3
1,D1,SODFL3718X115,SCHOTTKY_MBR0520LT1GDO-219,,Schottky Diode - Popular parts,MBR0520LT1G
1,Q1,SOT23-3,TRANSISTOR_PNPMMBT4403,,Generic PNP BJT,MMBT4403
1,R4,RESC1005X40,R_CHIP-0402(1005-METRIC),,Resistor Fixed - Generic,NO-FIT
1,U1,IC57_RP2040-L,RP2040IC57_RP2040-L,,,RP2040
1,SJ3,SJ_2S-TRACE,SOLDERJUMPERTRACE,,Solder Jumper,SOLDERJUMPERTRACE
2,"IO1, IO2",PAD.03X.03,TEST-POINT3,,SparkFun Test Points,TEST-POINT3
1,3.3V,PAD.03X.04,TEST-POINT3X4,,SparkFun Test Points,TEST-POINT3X4
3,"+5V, GND, ZOUT","B2,54","TPB2,54",,Test pad,"TPB2,54"
1,USB,CONN12_KH-TYPE-C-16P,USB-C(KH-TYPE-C-16P),,Shenzhen Kinghelm Elec KH-TYPE-C-16P,USB-C(KH-TYPE-C-16P)
1,D2,SOT-666_STM-L,USBLC6-2P6SOT-666_STM-L,,,USBLC6-2P6SOT-666_STM-L
1,U2,SOIC_128JVSIQ_WIN-L,W25Q128JVSIQSOIC_128JVSIQ_WIN-L,,,W25Q128

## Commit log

2023-10-18 Complete design of the board - before correction *if any*
2023-12-02 updated new ABL RP2040 schematics only
2023-12-08 Pre review finalization
2023-12-23 Logo, BOM, Centroids, Gerber files changes

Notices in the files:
parts and their libraries:
SparkFun-Connectors: Licensing: Creative Commons ShareAlike 4.0 International - https://creativecommons.org/licenses/by-sa/4.0
COPYRIGHT: Copyright (C) 2023 Ultra Librarian. All rights reserved.
Fracktal Misc Lib: COPYRIGHT: Copyright (C) 2018 Accelerated Designs. All rights reserved
